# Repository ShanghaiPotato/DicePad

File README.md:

Description: A hackpad that has 6 buttons for the 6 commonly used dice in Dungeons and Dragons. There is the d4, d6, d8, d10, d12, and d20 (nobody uses the percentile die). It will send the rolled number to the computer for whatever rollplaying game you want. Two LEDs will light up depending on the roll, green for a roll higher than half the maximum value of the die and red for a roll lower than half the maximum value of the die. 

Inspiration: Dungeons and Dragons is a game that I love, and being able to roll dice using a macropad sounds really fun and interesting. 

PCB:
Schematics - 

PCB - 

PCB Render - 

CAD: 
I used OnShape to create the case, it is something that is reall basic, but I plan on upgrading the case later depending on how all the parts come together.

Case - 

Firmware: 
I'm not that big of a programmer, so I chose KMK because I have some experience in python and it is much simpler to use.

BOM:
1x Seeed XIAO RP2040
6x [MX-Style switches](https://mechanicalkeyboards.com/products/cherry-mx-brown-hyperglide-45g-tactile?_pos=3&_fid=03915123d&_ss=c)
2x SK6812 MINI-E LEDs
4x M3x16mm screws

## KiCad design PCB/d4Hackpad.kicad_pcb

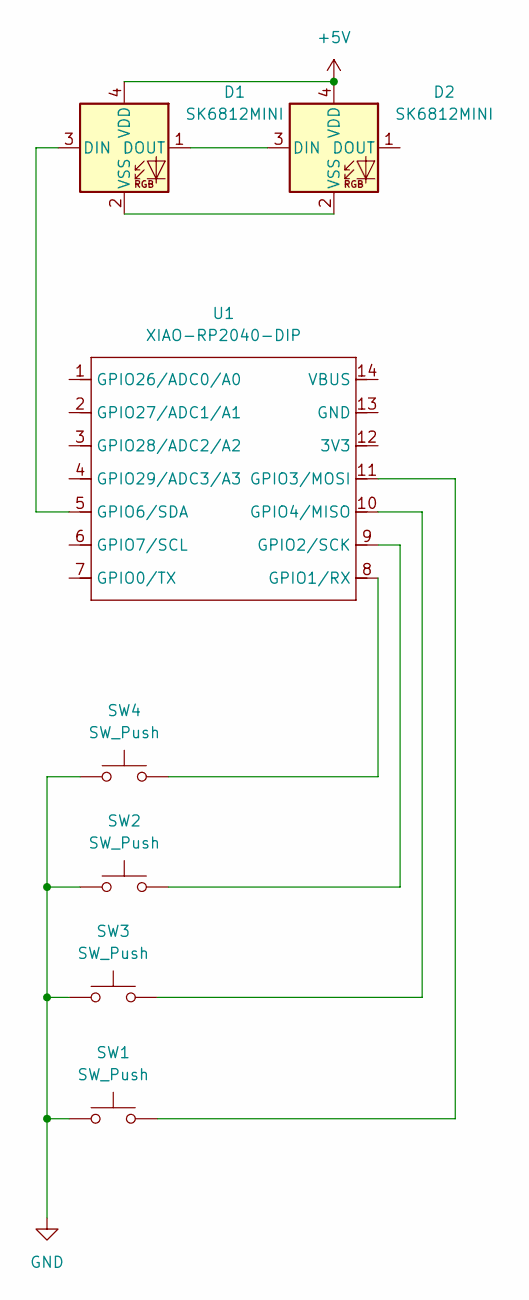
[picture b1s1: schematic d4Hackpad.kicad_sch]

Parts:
D1, D2: SK6812MINI; LED_SK6812MINI_PLCC4_3.5x3.5mm_P1.75mm
SW1, SW2, SW3, SW4: SW_Push; SW_Cherry_MX_1.00u_PCB
U1: XIAO-RP2040-DIP

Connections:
+5V: D1.4 (VDD), D2.4 (VDD)
GND: SW1.1, SW2.1, SW3.1, SW4.1
unnamed: D1.3 (DIN), U1.5 (GPIO6/SDA)
unnamed: D1.1 (DOUT), D2.3 (DIN)
unnamed: D1.2 (VSS), D2.2 (VSS)
unnamed: SW4.2, U1.8 (GPIO1/RX)
unnamed: SW2.2, U1.9 (GPIO2/SCK)
unnamed: SW1.2, U1.11 (GPIO3/MOSI)
unnamed: SW3.2, U1.10 (GPIO4/MISO)

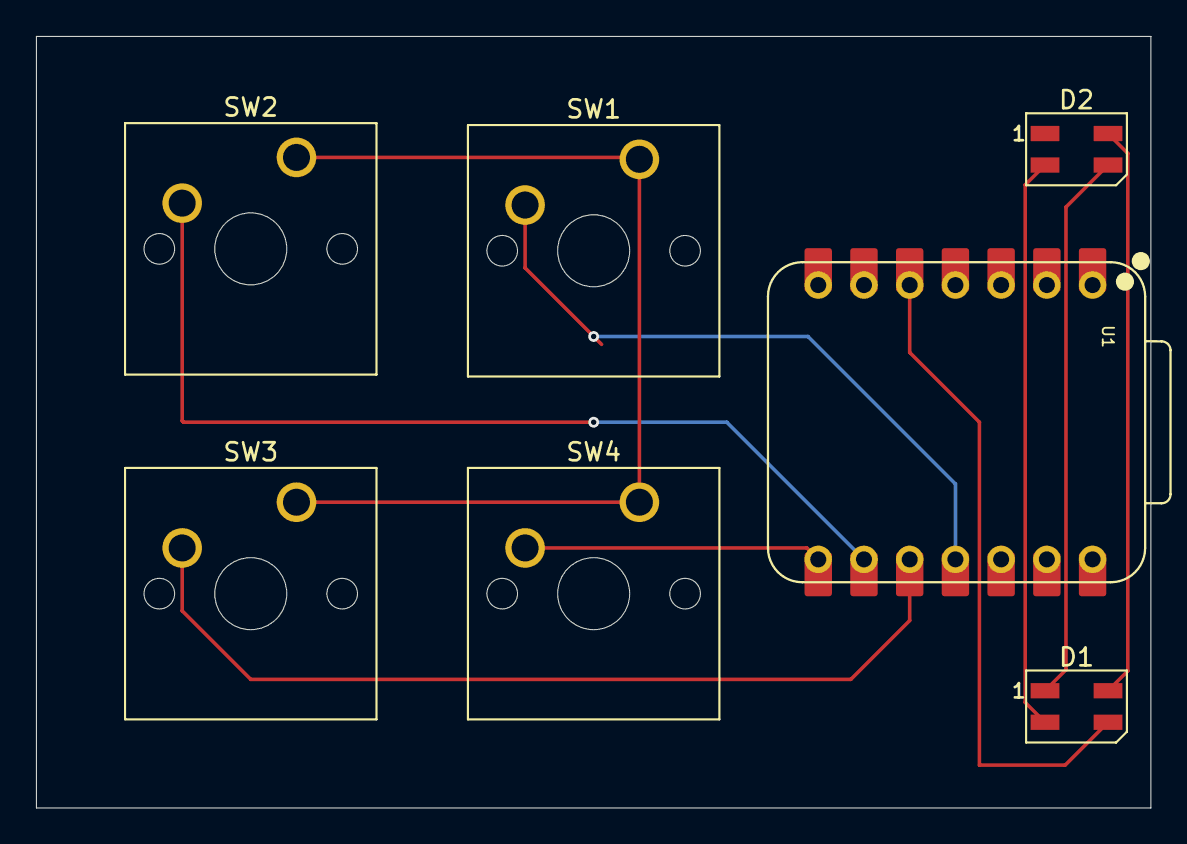
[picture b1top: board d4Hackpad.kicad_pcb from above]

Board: 2 copper layers, 61.9 x 42.9 mm, 7 parts (0 on the bottom side), 9 nets.

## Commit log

2025-06-27 Log 1
2025-06-29 Log 2
2025-06-30 Log 3
    Finished things up, hopefully everything that I need is there.
2025-07-08 Fixes
